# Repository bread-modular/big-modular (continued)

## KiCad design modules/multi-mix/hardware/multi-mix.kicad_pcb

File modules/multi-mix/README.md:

# multi-mix — digital 4-channel mixer with USB audio and MIDI (20HP)

modules/4mix's panel (4 channels with IN, SEND A, SEND B, VOL; RETURN A/B with levels; SEND A/B outs; OUT
jack over the MAIN knob, plus two host-assigned USB 1 / USB 2 outputs), widened to 20HP for the MCU board and its USB-C, rebuilt as a digital mixer: a PCM3168A codec and a CH32V307 MCU (both from modules/usb-audio-max)
do the mixing. Every knob is a DC divider read through a 74HC4067 mux and sent as MIDI CC (VOL as CC7). A TS MIDI IN jack
above the USB outs takes the rack's internal MIDI (controller modules) and passes it to the DAW as USB-MIDI. Over
USB the computer gets the 4 inputs and 2 returns (24-bit / 48 kHz) and can feed the returns. Units daisy-chain
through 2x5 CLK OUT -> CLK IN ribbons that share the codec clocks only, so stems recorded from several units
over their own USB ports stay sample-locked; each unit keeps its own MAIN OUT and sends (up to 4 units until
bench-tested).

**Status: carrier S5 / MCU S4 schematics (ERC 0, netlists asserted) + R3 manual routing of both boards at 20HP (carrier and MCU board DRC 0 / unconnected 0 / parity 0; single-sided MCU board on two 1x12 strips, three standoffs, panel P4). Datasheet review done (`docs/research.md` 6a); fab-review fixes applied (section 10); TS MIDI IN jack J11 above USB 1 -> PA10 USART1_RX, CLK IN J7 an unshrouded 2x5 header moved up (section 11, 2026-11-11). JLCPCB export in `jlcpcb/` (carrier bottom Economic 203 parts / 46 rows, MCU board top Economic 25 / 13, panel), not supplier-accepted. Open: J101 courtyard 0.53 mm to the MS3 notch and MS3 courtyard 0.98 mm to the edge, 10 Extended R/C placements (user decisions). Not built, no firmware.**

| Path | Contents |
|---|---|
| `hardware/multi-mix.kicad_sch` | Carrier: power, codec, inputs, outputs, knobs + mux, clock link, MIDI IN, MCU strips (PDF: `docs/multi-mix-schematic.pdf`) |
| `hardware/multi-mix-mcu.kicad_sch` | MCU board: CH32V307RCT6, USB-C, strips J112/J113 (PDF: `docs/multi-mix-mcu-schematic.pdf`) |
| `hardware/multi-mix.kicad_pcb`, `hardware/multi-mix-mcu.kicad_pcb` | R3 boards, 4 layers, placed and routed by hand (carrier: all SMD on B; MCU board: every part on F) |
| `panels/front-pcb/multi-mix-panel.kicad_pcb` | 20HP passive FR4 panel P4 (NPTH holes, USB-C slot, labels) |
| `jlcpcb/` | JLCPCB export: `main/` carrier + panel, `mcu/` MCU board (`jlcpcb/README.md`: upload map, hand-soldered parts, audit, order gates) |
| `docs/geometry.json` | Placement contract (panel frame) |
| `docs/research.md` | Brief, architecture, decisions, clock-link pinout, MCU pins and strip maps, sourcing, datasheet review, placement, S2/S3 changes and R1 routing, fab-review fixes (S4/R2), MIDI IN (S5/R3), open items |
| `tools/` | Schematic generator + circuit tables, footprint import, project files, shared-tool profiles, `check_usb.py` (MCU USB routing check) |

Rebuild (from `modules/multi-mix`):

```sh
python3 -B tools/import_footprints.py
python3 -B tools/build_schematic.py
python3 -B tools/build_project.py
# tools/build_layout.py wrote the P3 boards: do NOT run it, the boards are placed and routed by hand
kicad-cli sch erc --severity-all --format json -o docs/erc/multi-mix-erc.json hardware/multi-mix.kicad_sch
kicad-cli sch erc --severity-all --format json -o docs/erc/multi-mix-mcu-erc.json hardware/multi-mix-mcu.kicad_sch
```

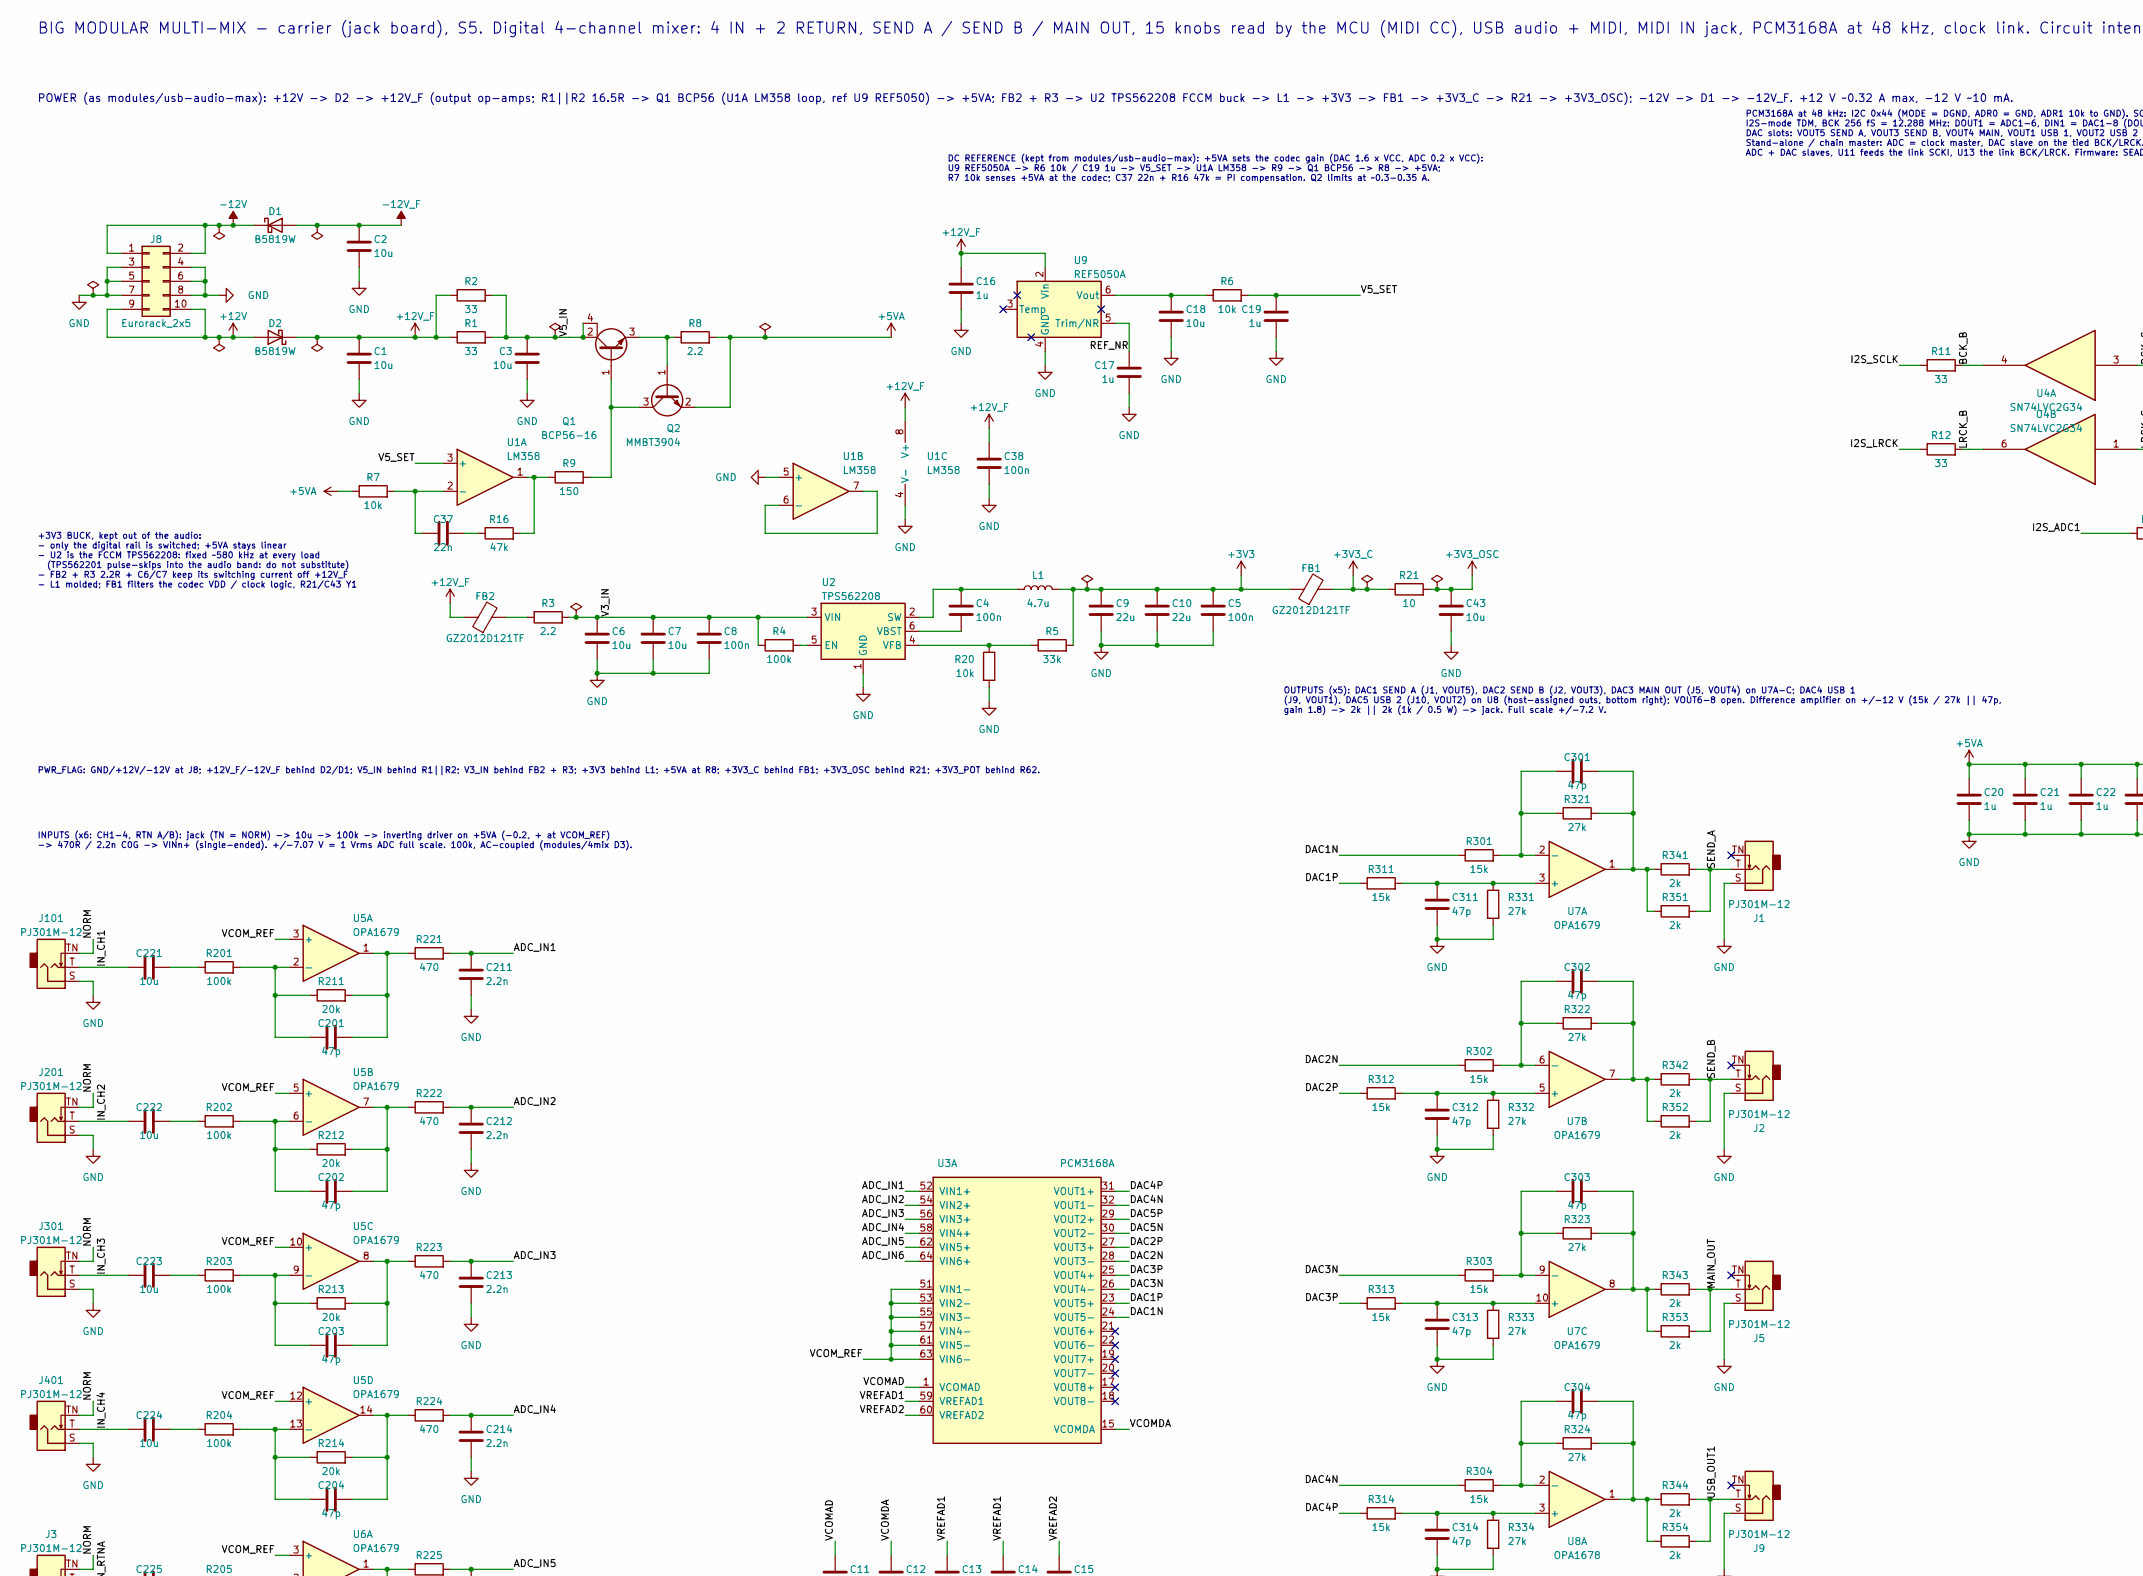
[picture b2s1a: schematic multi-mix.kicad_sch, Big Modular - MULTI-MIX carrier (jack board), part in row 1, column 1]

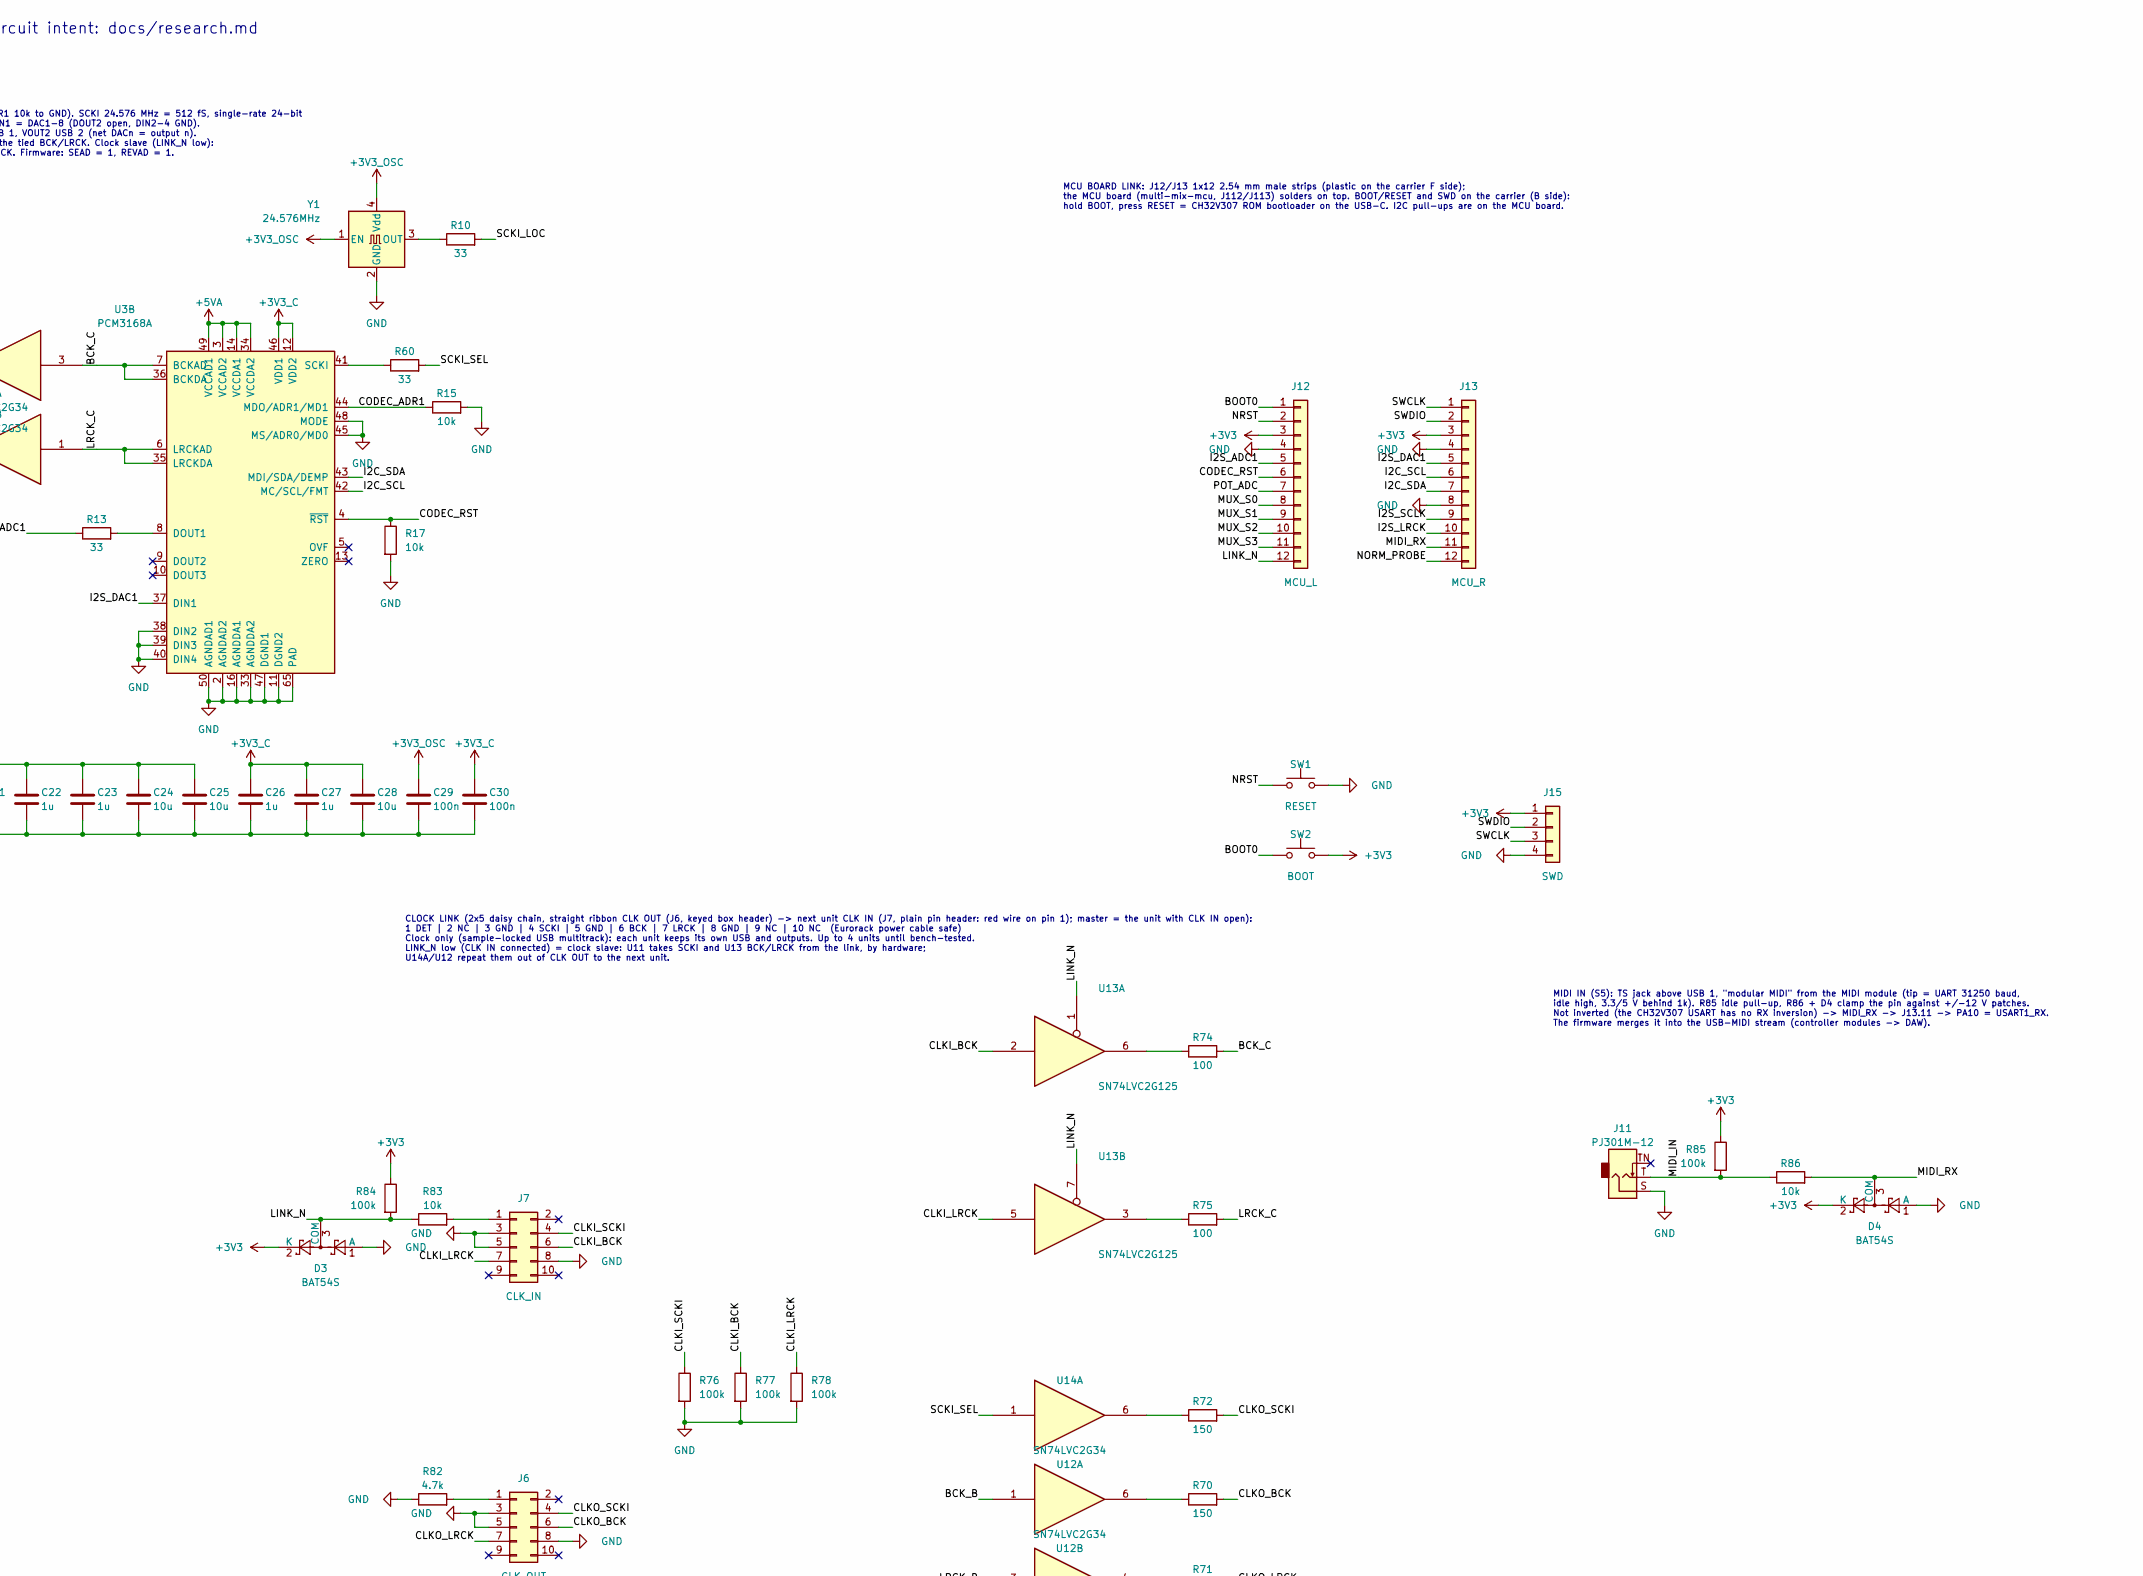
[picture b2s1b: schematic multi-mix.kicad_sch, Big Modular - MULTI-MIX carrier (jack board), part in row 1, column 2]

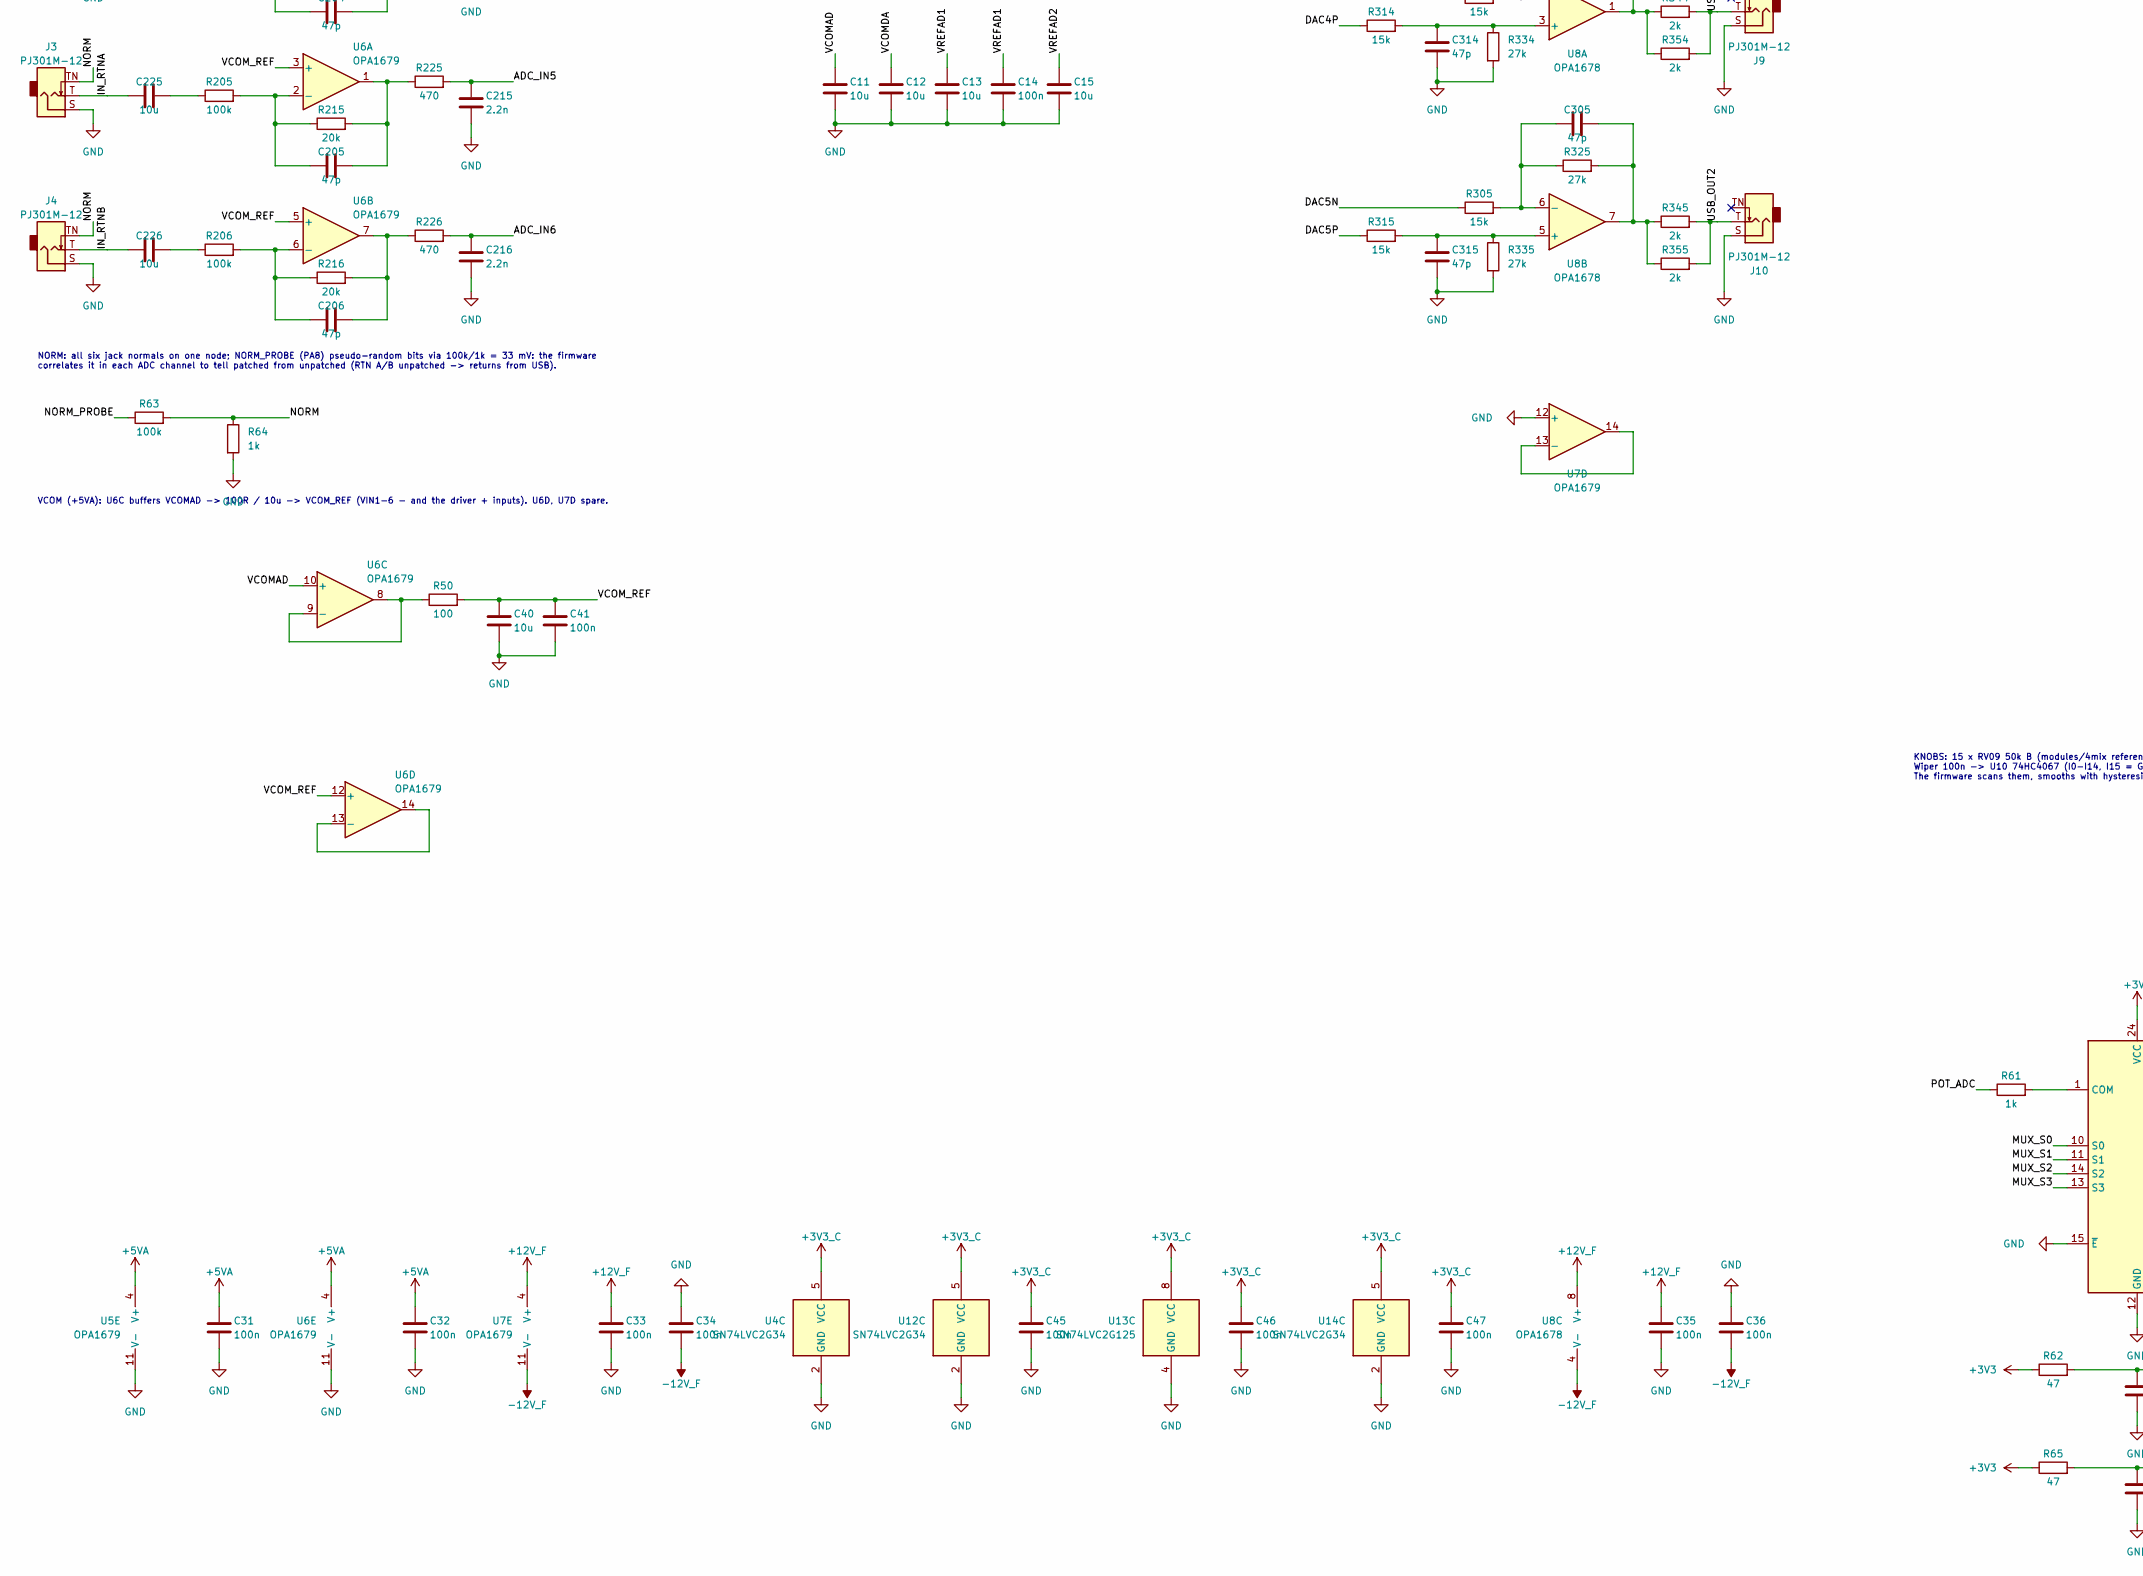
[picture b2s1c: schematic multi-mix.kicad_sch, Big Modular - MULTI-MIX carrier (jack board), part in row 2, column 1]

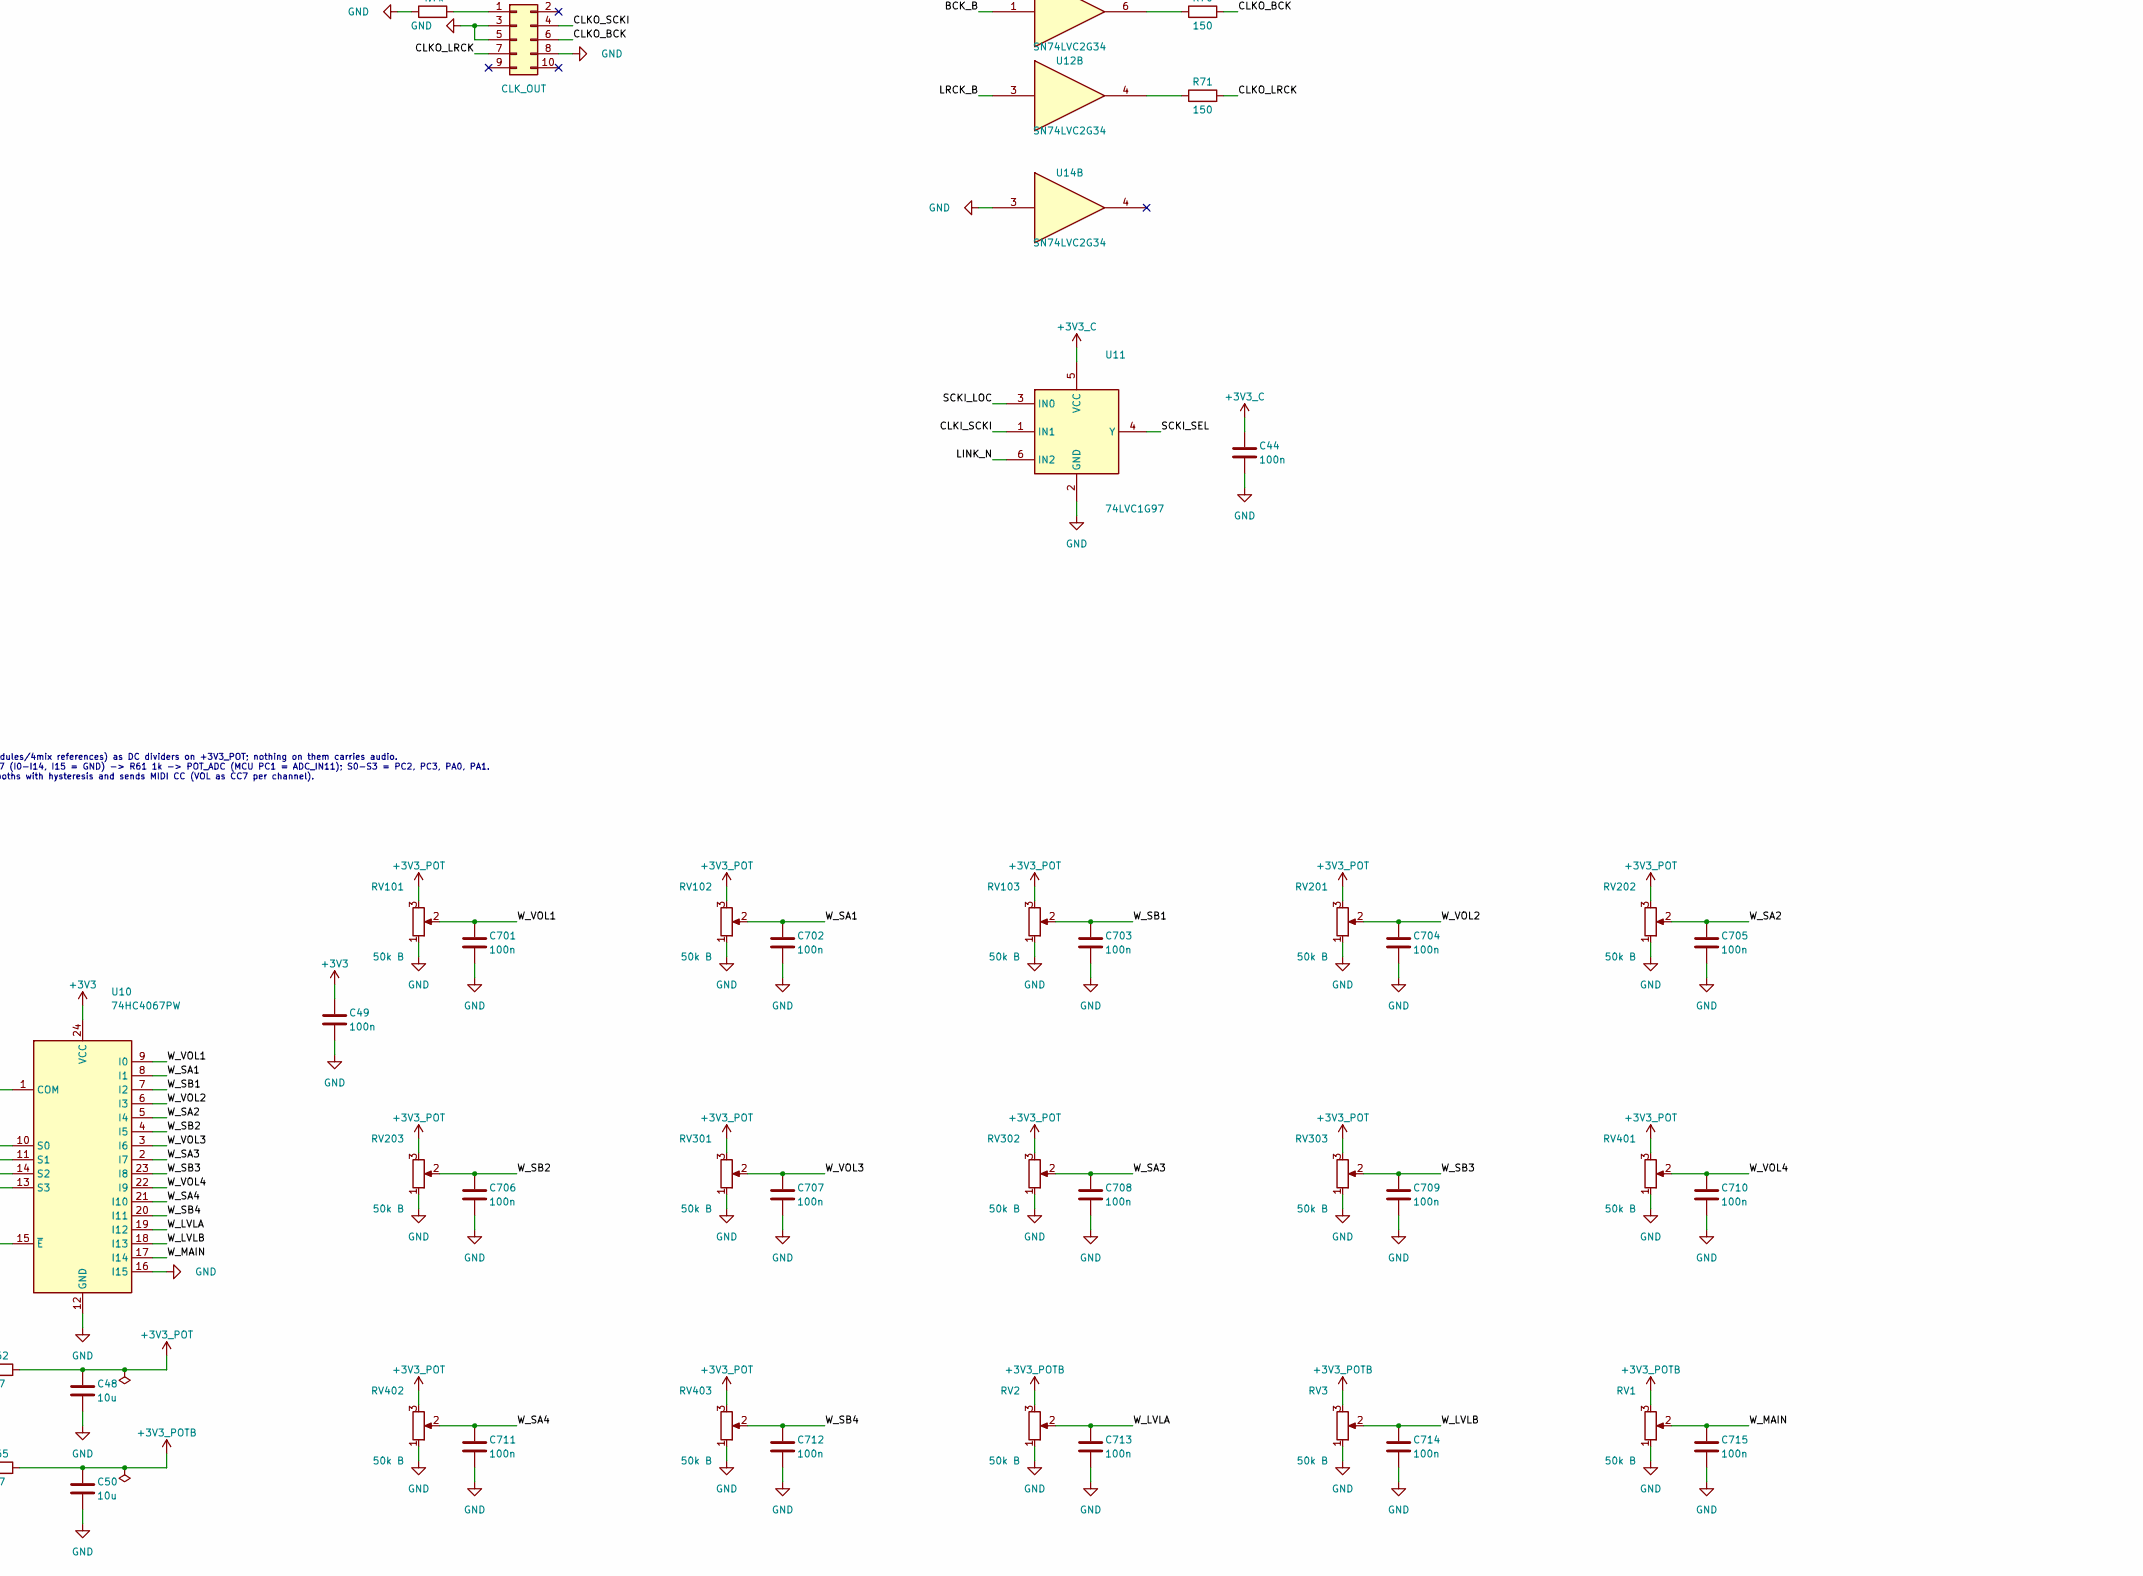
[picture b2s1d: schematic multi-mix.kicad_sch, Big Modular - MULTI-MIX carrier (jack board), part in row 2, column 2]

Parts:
C1, C2, C3, C11, C12, C13, C15, C18, C24, C25, C28, C40, C43, C48, C50, C221, C222, C223, C224, C225, C226: 10u; C_0805_2012Metric; Voltage 25V; MPN CL21A106KAYNNNE; LCSC C15850
C4, C5, C8, C14, C29, C30, C31, C32, C33, C34, C35, C36, C38, C41, C44, C45, C46, C47, C49, C701, C702, C703, C704, C705, C706, C707, C708, C709, C710, C711, C712, C713, C714, C715: 100n; C_0603_1608Metric; Voltage 50V; MPN CC0603KRX7R9BB104; LCSC C14663
C6, C7: 10u; C_1206_3216Metric; Voltage 50V; MPN CL31A106KBHNNNE; LCSC C13585
C9, C10: 22u; C_0805_2012Metric; Voltage 25V; MPN CL21A226MAQNNNE; LCSC C45783
C16, C17, C19, C20, C22, C23, C26: 1u; C_0603_1608Metric; Voltage 50V; MPN CL10A105KB8NNNC; LCSC C15849
C21, C27: 1u; C_0402_1005Metric; Voltage 25V; MPN CL05A105KA5NQNC; LCSC C52923
C37: 22n; C_0603_1608Metric; Voltage 50V; MPN CL10B223KB8NNNC; LCSC C21122
C201, C202, C203, C204, C205, C206, C301, C302, C303, C304, C305, C311, C312, C313, C314, C315: 47p; C_0603_1608Metric; Voltage 50V; MPN CL10C470JB8NNNC; LCSC C1671
C211, C212, C213, C214, C215, C216: 2.2n; C_0603_1608Metric; Voltage 50V; MPN CL10C222JB8NNNC; LCSC C33353
D1, D2: B5819W; D_SOD-123; MPN B5819W SL; LCSC C8598
D3, D4: BAT54S; SOT-23; MPN BAT54S,215; LCSC C47546
FB1, FB2: GZ2012D121TF; C_0805_2012Metric; MPN GZ2012D121TF; LCSC C5671
J1, J2, J3, J4, J5, J9, J10, J11, J101, J201, J301, J401: PJ301M-12; Jack_3.5mm_QingPu_WQP-PJ301M-12_Vertical
J6: CLK_OUT; IDC-Header_2x05_P2.54mm_Vertical
J7: CLK_IN; PinHeader_2x05_P2.54mm_Vertical
J8: Eurorack_2x5; PinHeader_2x05_P2.54mm_Vertical
J12: MCU_L; PinHeader_1x12_P2.54mm_Vertical; MPN 2.54 mm 1x12 male pin header (2.5 mm pl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
J13: MCU_R; PinHeader_1x12_P2.54mm_Vertical; MPN 2.54 mm 1x12 male pin header (2.5 mm pl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
J15: SWD; PinHeader_1x04_P2.54mm_Vertical
L1: 4.7u; L_Sunlord_MWSA0402S; MPN MWSA0402S-4R7MT; LCSC C408337
Q1: BCP56-16; SOT-223; MPN BCP56-16,115; LCSC C92221
Q2: MMBT3904; SOT-23; MPN MMBT3904; LCSC C20526
R1, R2: 33; R_2512_6332Metric; MPN 25121WF330JT4E; LCSC C53728
R3, R8: 2.2; R_1206_3216Metric; Tolerance 1%; MPN AC1206FR-072R2L; LCSC C144499
R4, R63, R76, R77, R78, R84, R85, R201, R202, R203, R204, R205, R206: 100k; R_0603_1608Metric; MPN 0603WAF1003T5E; LCSC C25803
R5: 33k; R_0603_1608Metric; MPN 0603WAF3302T5E; LCSC C4216
R6, R7, R15, R17, R20, R83, R86: 10k; R_0603_1608Metric; MPN 0603WAF1002T5E; LCSC C25804
R9, R70, R71, R72: 150; R_0603_1608Metric; MPN 0603WAF1500T5E; LCSC C22808
R10, R11, R12, R13, R60: 33; R_0603_1608Metric; MPN 0603WAF330JT5E; LCSC C23140
R16: 47k; R_0603_1608Metric; MPN 0603WAF4702T5E; LCSC C25819
R21: 10; R_0603_1608Metric; MPN 0603WAF100JT5E; LCSC C22859
R50, R74, R75: 100; R_0603_1608Metric; MPN 0603WAF1000T5E; LCSC C22775
R61, R64: 1k; R_0603_1608Metric; MPN 0603WAF1001T5E; LCSC C21190
R62, R65: 47; R_0603_1608Metric; MPN 0603WAF470JT5E; LCSC C23182
R82: 4.7k; R_0603_1608Metric; MPN 0603WAF4701T5E; LCSC C23162
R211, R212, R213, R214, R215, R216: 20k; R_0603_1608Metric; MPN 0603WAF2002T5E; LCSC C4184
R221, R222, R223, R224, R225, R226: 470; R_0603_1608Metric; MPN 0603WAF4700T5E; LCSC C23179
R301, R302, R303, R304, R305, R311, R312, R313, R314, R315: 15k; R_0603_1608Metric; Tolerance 1%; MPN 0603WAF1502T5E; LCSC C22809
R321, R322, R323, R324, R325, R331, R332, R333, R334, R335: 27k; R_0603_1608Metric; Tolerance 1%; MPN 0603WAF2702T5E; LCSC C22967
R341, R342, R343, R344, R345, R351, R352, R353, R354, R355: 2k; R_1206_3216Metric; Tolerance 1%; MPN 1206W4F2001T5E; LCSC C17944
RV1, RV2, RV3, RV101, RV102, RV103, RV201, RV202, RV203, RV301, RV302, RV303, RV401, RV402, RV403: 50k B; Potentiometer_RV09
SW1: RESET; K2-1808SN-A4SW-01; MPN K2-1808SN-A4SW-01; LCSC C92589
SW2: BOOT; K2-1808SN-A4SW-01; MPN K2-1808SN-A4SW-01; LCSC C92589
U1: LM358; SOIC-8_3.9x4.9mm_P1.27mm; MPN LM358DR2G; LCSC C7950
U2: TPS562208; SOT-23-6; MPN TPS562208DDCR; LCSC C91301
U3: PCM3168A; PCM3168A_HTQFP-64-1EP_10x10mm_P0.5mm_EP8x8mm_Mask7.4x7.4mm_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; MPN PCM3168APAPR; LCSC C529289
U4, U12, U14: SN74LVC2G34; SOT-363_SC-70-6; MPN SN74LVC2G34DCKR; LCSC C14461
U5, U6, U7: OPA1679; SOIC-14_3.9x8.7mm_P1.27mm; MPN OPA1679IDR; LCSC C2878631
U8: OPA1678; SOIC-8_3.9x4.9mm_P1.27mm; MPN OPA1678IDR; LCSC C192421
U9: REF5050A; SOIC-8_3.9x4.9mm_P1.27mm; MPN REF5050AIDR; LCSC C27804
U10: 74HC4067PW; TSSOP-24_4.4x7.8mm_P0.65mm; MPN 74HC4067PW,118; LCSC C179326
U11: 74LVC1G97; SOT-363_SC-70-6; MPN 74LVC1G97DW-7; LCSC C460532
U13: SN74LVC2G125; SSOP-8_2.95x2.8mm_P0.65mm; MPN SN74LVC2G125DCTR; LCSC C206035
Y1: 24.576MHz; Oscillator_SMD_Abracon_ASE-4Pin_3.2x2.5mm; MPN OT2EL4C4JI-111OLP-24.576M; LCSC C5203547

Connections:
+3V3: C5.1, C9.1, C10.1, C49.1, D3.2 (K), D4.2 (K), FB1.1, J12.3, J13.3, J15.1, L1.2, R5.2, R62.1, R65.1, R84.1, R85.1, SW2.2, U10.24 (VCC)
+3V3_C: C26.1, C27.1, C28.1, C30.1, C44.1, C45.1, C46.1, C47.1, FB1.2, R21.1, U3.12 (VDD2), U3.46 (VDD1), U4.5 (VCC), U11.5 (VCC), U12.5 (VCC), U13.8 (VCC), U14.5 (VCC)
+3V3_OSC: C29.1, C43.1, R21.2, Y1.1 (EN), Y1.4 (Vdd)
+3V3_POT: C48.1, R62.2, RV101.3, RV102.3, RV103.3, RV201.3, RV202.3, RV203.3, RV301.3, RV302.3, RV303.3, RV401.3, RV402.3, RV403.3
+3V3_POTB: C50.1, R65.2, RV1.3, RV2.3, RV3.3
+5VA: C20.1, C21.1, C22.1, C23.1, C24.1, C25.1, C31.1, C32.1, Q2.2 (E), R7.1, R8.2, U3.3 (VCCAD2), U3.14 (VCCDA1), U3.34 (VCCDA2), U3.49 (VCCAD1), U5.4 (V+), U6.4 (V+)
+12V: D2.2 (A), J8.9, J8.10
+12V_F: C1.1, C16.1, C33.1, C35.1, C38.1, D2.1 (K), FB2.1, R1.1, R2.1, U1.8 (V+), U7.4 (V+), U8.8 (V+), U9.2 (Vin)
-12V: D1.1 (K), J8.1, J8.2
-12V_F: C2.2, C34.2, C36.2, D1.2 (A), U7.11 (V-), U8.4 (V-)
/ADC_IN1: C211.1, R221.2, U3.52 (VIN1+)
/ADC_IN2: C212.1, R222.2, U3.54 (VIN2+)
/ADC_IN3: C213.1, R223.2, U3.56 (VIN3+)
/ADC_IN4: C214.1, R224.2, U3.58 (VIN4+)
/ADC_IN5: C215.1, R225.2, U3.62 (VIN5+)
/ADC_IN6: C216.1, R226.2, U3.64 (VIN6+)
/BCK_B: R11.2, U4.4, U12.1
/BCK_C: R74.2, U3.7 (BCKAD), U3.36 (BCKDA), U4.3
/BOOT0: J12.1, SW2.1
/CLKI_BCK: J7.6, R77.1, U13.2
/CLKI_LRCK: J7.7, R78.1, U13.5
/CLKI_SCKI: J7.4, R76.1, U11.1 (IN1)
/CLKO_BCK: J6.6, R70.2
/CLKO_LRCK: J6.7, R71.2
/CLKO_SCKI: J6.4, R72.2
/CODEC_ADR1: R15.1, U3.44 (MDO/ADR1/MD1)
/CODEC_RST: J12.6, R17.1, U3.4 (~RST)
/DAC1N: R301.1, U3.24 (VOUT5-)
/DAC1P: R311.1, U3.23 (VOUT5+)
/DAC2N: R302.1, U3.28 (VOUT3-)
/DAC2P: R312.1, U3.27 (VOUT3+)
/DAC3N: R303.1, U3.26 (VOUT4-)
/DAC3P: R313.1, U3.25 (VOUT4+)
/DAC4N: R304.1, U3.32 (VOUT1-)
/DAC4P: R314.1, U3.31 (VOUT1+)
/DAC5N: R305.1, U3.30 (VOUT2-)
/DAC5P: R315.1, U3.29 (VOUT2+)
/I2C_SCL: J13.6, U3.42 (MC/SCL/FMT)
/I2C_SDA: J13.7, U3.43 (MDI/SDA/DEMP)
/I2S_ADC1: J12.5, R13.1
/I2S_DAC1: J13.5, U3.37 (DIN1)
/I2S_LRCK: J13.10, R12.1
/I2S_SCLK: J13.9, R11.1
/IN_CH1: C221.1, J101.T
/IN_CH2: C222.1, J201.T
/IN_CH3: C223.1, J301.T
/IN_CH4: C224.1, J401.T
/IN_RTNA: C225.1, J3.T
/IN_RTNB: C226.1, J4.T
/LINK_N: D3.3 (COM), J12.12, R83.1, R84.2, U11.6 (IN2), U13.1, U13.7
/LRCK_B: R12.2, U4.6, U12.3
/LRCK_C: R75.2, U3.6 (LRCKAD), U3.35 (LRCKDA), U4.1
/MAIN_OUT: J5.T, R343.2, R353.2
/MIDI_IN: J11.T, R85.2, R86.1
/MIDI_RX: D4.3 (COM), J13.11, R86.2
/MUX_S0: J12.8, U10.10 (S0)
/MUX_S1: J12.9, U10.11 (S1)
/MUX_S2: J12.10, U10.14 (S2)
/MUX_S3: J12.11, U10.13 (S3)
/NORM: J3.TN, J4.TN, J101.TN, J201.TN, J301.TN, J401.TN, R63.2, R64.1
/NORM_PROBE: J13.12, R63.1
/NRST: J12.2, SW1.1
/POT_ADC: J12.7, R61.1
/REF_NR: C17.1, U9.5 (Trim/NR)
/SCKI_LOC: R10.2, U11.3 (IN0)
/SCKI_SEL: R60.2, U11.4 (Y), U14.1
/SEND_A: J1.T, R341.2, R351.2
/SEND_B: J2.T, R342.2, R352.2
/SWCLK: J13.1, J15.3
/SWDIO: J13.2, J15.2
/USB_OUT1: J9.T, R344.2, R354.2
/USB_OUT2: J10.T, R345.2, R355.2
/V3_IN: C6.1, C7.1, C8.1, R3.2, R4.1, U2.3 (VIN)
/V5_IN: C3.1, Q1.2 (C), Q1.4 (C), R1.2, R2.2
/V5_SET: C19.1, R6.2, U1.3 (+)
/VCOMAD: C11.1, U3.1 (VCOMAD), U6.10 (+)
/VCOMDA: C12.1, U3.15 (VCOMDA)
/VCOM_REF: C40.1, C41.1, R50.2, U3.51 (VIN1-), U3.53 (VIN2-), U3.55 (VIN3-), U3.57 (VIN4-), U3.61 (VIN5-), U3.63 (VIN6-), U5.3 (+), U5.5 (+), U5.10 (+), U5.12 (+), U6.3 (+), U6.5 (+), U6.12 (+)
/VREFAD1: C13.1, C14.1, U3.59 (VREFAD1)
/VREFAD2: C15.1, U3.60 (VREFAD2)
/W_LVLA: C713.1, RV2.2, U10.19 (I12)
/W_LVLB: C714.1, RV3.2, U10.18 (I13)
/W_MAIN: C715.1, RV1.2, U10.17 (I14)
/W_SA1: C702.1, RV102.2, U10.8 (I1)
/W_SA2: C705.1, RV202.2, U10.5 (I4)
/W_SA3: C708.1, RV302.2, U10.2 (I7)
/W_SA4: C711.1, RV402.2, U10.21 (I10)
/W_SB1: C703.1, RV103.2, U10.7 (I2)
/W_SB2: C706.1, RV203.2, U10.4 (I5)
/W_SB3: C709.1, RV303.2, U10.23 (I8)
/W_SB4: C712.1, RV403.2, U10.20 (I11)
/W_VOL1: C701.1, RV101.2, U10.9 (I0)
/W_VOL2: C704.1, RV201.2, U10.6 (I3)
/W_VOL3: C707.1, RV301.2, U10.3 (I6)
/W_VOL4: C710.1, RV401.2, U10.22 (I9)
GND: C1.2, C2.1, C3.2, C5.2, C6.2, C7.2, C8.2, C9.2, C10.2, C11.2, C12.2, C13.2, C14.2, C15.2, C16.2, C17.2, C18.2, C19.2, C20.2, C21.2, C22.2, C23.2, C24.2, C25.2, C26.2, C27.2, C28.2, C29.2, C30.2, C31.2, C32.2, C33.2, C34.1, C35.2, C36.1, C38.2, C40.2, C41.2, C43.2, C44.2, C45.2, C46.2, C47.2, C48.2, C49.2, C50.2, C211.2, C212.2, C213.2, C214.2, C215.2, C216.2, C311.2, C312.2, C313.2, C314.2, C315.2, C701.2, C702.2, C703.2, C704.2, C705.2, C706.2, C707.2, C708.2, C709.2, C710.2, C711.2, C712.2, C713.2, C714.2, C715.2, D3.1 (A), D4.1 (A), J1.S, J2.S, J3.S, J4.S, J5.S, J6.3, J6.5, J6.8, J7.3, J7.5, J7.8, J8.3, J8.4, J8.5, J8.6, J8.7, J8.8, J9.S, J10.S, J11.S, J12.4, J13.4, J13.8, J15.4, J101.S, J201.S, J301.S, J401.S, R15.2, R17.2, R20.2, R64.2, R76.2, R77.2, R78.2, R82.1, R331.2, R332.2, R333.2, R334.2, R335.2, RV1.1, RV2.1, RV3.1, RV101.1, RV102.1, RV103.1, RV201.1, RV202.1, RV203.1, RV301.1, RV302.1, RV303.1, RV401.1, RV402.1, RV403.1, SW1.2, U1.4 (V-), U1.5 (+), U2.1 (GND), U3.2 (AGNDAD2), U3.11 (DGND2), U3.16 (AGNDDA1), U3.33 (AGNDDA2), U3.38 (DIN2), U3.39 (DIN3), U3.40 (DIN4), U3.45 (MS/ADR0/MD0), U3.47 (DGND1), U3.48 (MODE), U3.50 (AGNDAD1), U3.65 (PAD), U4.2 (GND), U5.11 (V-), U6.11 (V-), U7.12 (+), U9.4 (GND), U10.12 (GND), U10.15 (~E), U10.16 (I15), U11.2 (GND), U12.2 (GND), U13.4 (GND), U14.2 (GND), U14.3, Y1.2 (GND)
unnamed: C37.2, R16.1
unnamed: C201.2, R211.2, R221.1, U5.1
unnamed: C202.2, R212.2, R222.1, U5.7
unnamed: C203.2, R213.2, R223.1, U5.8
unnamed: C204.2, R214.2, R224.1, U5.14
unnamed: C205.2, R215.2, R225.1, U6.1
unnamed: C206.2, R216.2, R226.1, U6.7
unnamed: C221.2, R201.1
unnamed: C222.2, R202.1
unnamed: C223.2, R203.1
unnamed: C224.2, R204.1
unnamed: C225.2, R205.1
unnamed: C226.2, R206.1
unnamed: C301.2, R321.2, R341.1, R351.1, U7.1
unnamed: C302.2, R322.2, R342.1, R352.1, U7.7
unnamed: C303.2, R323.2, R343.1, R353.1, U7.8
unnamed: C304.2, R324.2, R344.1, R354.1, U8.1
unnamed: C305.2, R325.2, R345.1, R355.1, U8.7
unnamed: FB2.2, R3.1
unnamed: J6.1, R82.2
unnamed: J7.1, R83.2
unnamed: Q1.1 (B), Q2.3 (C), R9.2
unnamed: Q1.3 (E), Q2.1 (B), R8.1
unnamed: R9.1, R16.2, U1.1
unnamed: R70.1, U12.6
unnamed: R71.1, U12.4
unnamed: R72.1, U14.6
unnamed: R74.1, U13.6
unnamed: R75.1, U13.3
unnamed: C37.1, R7.2, U1.2 (-)
unnamed: U1.6 (-), U1.7
unnamed: R4.2, U2.5 (EN)
unnamed: C4.1, L1.1, U2.2 (SW)
unnamed: C4.2, U2.6 (VBST)
unnamed: R5.1, R20.1, U2.4 (VFB)
unnamed: R13.2, U3.8 (DOUT1)
unnamed: R60.1, U3.41 (SCKI)
unnamed: C201.1, R201.2, R211.1, U5.2 (-)
unnamed: C202.1, R202.2, R212.1, U5.6 (-)
unnamed: C203.1, R203.2, R213.1, U5.9 (-)
unnamed: C204.1, R204.2, R214.1, U5.13 (-)
unnamed: C205.1, R205.2, R215.1, U6.2 (-)
unnamed: C206.1, R206.2, R216.1, U6.6 (-)
unnamed: R50.1, U6.8, U6.9 (-)
unnamed: U6.13 (-), U6.14
unnamed: C311.1, R311.2, R331.1, U7.3 (+)
unnamed: C301.1, R301.2, R321.1, U7.2 (-)
unnamed: C312.1, R312.2, R332.1, U7.5 (+)
unnamed: C302.1, R302.2, R322.1, U7.6 (-)
unnamed: C313.1, R313.2, R333.1, U7.10 (+)
unnamed: C303.1, R303.2, R323.1, U7.9 (-)
unnamed: U7.13 (-), U7.14
unnamed: C314.1, R314.2, R334.1, U8.3 (+)
unnamed: C304.1, R304.2, R324.1, U8.2 (-)
unnamed: C315.1, R315.2, R335.1, U8.5 (+)
unnamed: C305.1, R305.2, R325.1, U8.6 (-)
unnamed: C18.1, R6.1, U9.6 (Vout)
unnamed: R61.2, U10.1 (COM)
unnamed: R10.1, Y1.3 (OUT)

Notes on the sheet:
PCM3168A at 48 kHz: I2C 0x44 (MODE = DGND, ADR0 = GND, ADR1 10k to GND). SCKI 24.576 MHz = 512 fS, single-rate 24-bit I2S-mode TDM, BCK 256 fS = 12.288 MHz: DOUT1 = ADC1-6, DIN1 = DAC1-8 (DOUT2 open, DIN2-4 GND). DAC slots: VOUT5 SEND A, VOUT3 SEND B, VOUT4 MAIN, VOUT1 USB 1, VOUT2 USB 2 (net DACn 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
BIG MODULAR MULTI-MIX - carrier (jack board), S5. Digital 4-channel mixer: 4 IN + 2 RETURN, SEND A / SEND B / MAIN OUT, 15 knobs read by the MCU (MIDI CC), USB audio + MIDI, MIDI IN jack, PCM3168A at 48 kHz, clock link. Circuit intent: docs/research.md
MCU BOARD LINK: J12/J13 1x12 2.54 mm male strips (plastic on the carrier F side); the MCU board (multi-mix-mcu, J112/J113) solders on top. BOOT/RESET and SWD on the carrier (B side): hold BOOT, press RESET = CH32V307 ROM bootloader on the USB-C. I2C pull-ups are on the MCU board.
PWR_FLAG: GND/+12V/-12V at J8; +12V_F/-12V_F behind D2/D1; V5_IN behind R1||R2; V3_IN behind FB2 + R3; +3V3 behind L1; +5VA at R8; +3V3_C behind FB1; +3V3_OSC behind R21; +3V3_POT behind R62.
NORM: all six jack normals on one node; NORM_PROBE (PA8) pseudo-random bits via 100k/1k = 33 mV: the firmware correlates it in each ADC channel to tell patched from unpatched (RTN A/B unpatched -> returns from USB).
VCOM (+5VA): U6C buffers VCOMAD -> 100R / 10u -> VCOM_REF (VIN1-6 - and the driver + inputs). U6D, U7D spare.
INPUTS (x6: CH1-4, RTN A/B): jack (TN = NORM) -> 10u -> 100k -> inverting driver on +5VA (-0.2, + at VCOM_REF) -> 470R / 2.2n C0G -> VINn+ (single-ended). +/-7.07 V = 1 Vrms ADC full scale. 100k, AC-coupled (modules/4mix D3).
OUTPUTS (x5): DAC1 SEND A (J1, VOUT5), DAC2 SEND B (J2, VOUT3), DAC3 MAIN OUT (J5, VOUT4) on U7A-C; DAC4 USB 1 (J9, VOUT1), DAC5 USB 2 (J10, VOUT2) on U8 (host-assigned outs, bottom right); VOUT6-8 open. Difference amplifier on +/-12 V (15k / 27k || 47p, gain 1.8) -> 2k || 2k (1k / 0.5 W) -> jack. 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
+3V3 BUCK, kept out of the audio: - only the digital rail is switched; +5VA stays linear - U2 is the FCCM TPS562208: fixed ~580 kHz at every load (TPS562201 pulse-skips into the audio band: do not substitute) - FB2 + R3 2.2R + C6/C7 keep its switching current off +12V_F - L1 molded; FB1 filters the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
DC REFERENCE (kept from modules/usb-audio-max): +5VA sets the codec gain (DAC 1.6 x VCC, ADC 0.2 x VCC): U9 REF5050A -> R6 10k / C19 1u -> V5_SET -> U1A LM358 -> R9 -> Q1 BCP56 -> R8 -> +5VA; R7 10k senses +5VA at the codec; C37 22n + R16 47k = PI compensation. Q2 limits at ~0.3-0.35 A.
KNOBS: 15 x RV09 50k B (modules/4mix references) as DC dividers on +3V3_POT; nothing on them carries audio. Wiper 100n -> U10 74HC4067 (I0-I14, I15 = GND) -> R61 1k -> POT_ADC (MCU PC1 = ADC_IN11); S0-S3 = PC2, PC3, PA0, PA1. The firmware scans them, smooths with hysteresis and sends MIDI CC (VOL a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
CLOCK LINK (2x5 daisy chain, straight ribbon CLK OUT (J6, keyed box header) -> next unit CLK IN (J7, plain pin header: red wire on pin 1); master = the unit with CLK IN open): 1 DET | 2 NC | 3 GND | 4 SCKI | 5 GND | 6 BCK | 7 LRCK | 8 GND | 9 NC | 10 NC (Eurorack power cable safe) Clock only (sampl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
MIDI IN (S5): TS jack above USB 1, "modular MIDI" from the MIDI module (tip = UART 31250 baud, idle high, 3.3/5 V behind 1k). R85 idle pull-up, R86 + D4 clamp the pin against +/-12 V patches. Not inverted (the CH32V307 USART has no RX inversion) -> MIDI_RX -> J13.11 -> PA10 = USART1_RX. The firmwar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
POWER (as modules/usb-audio-max): +12V -> D2 -> +12V_F (output op-amps; R1||R2 16.5R -> Q1 BCP56 (U1A LM358 loop, ref U9 REF5050) -> +5VA; FB2 + R3 -> U2 TPS562208 FCCM buck -> L1 -> +3V3 -> FB1 -> +3V3_C -> R21 -> +3V3_OSC); -12V -> D1 -> -12V_F. +12 V ~0.32 A max, -12 V ~10 mA.
